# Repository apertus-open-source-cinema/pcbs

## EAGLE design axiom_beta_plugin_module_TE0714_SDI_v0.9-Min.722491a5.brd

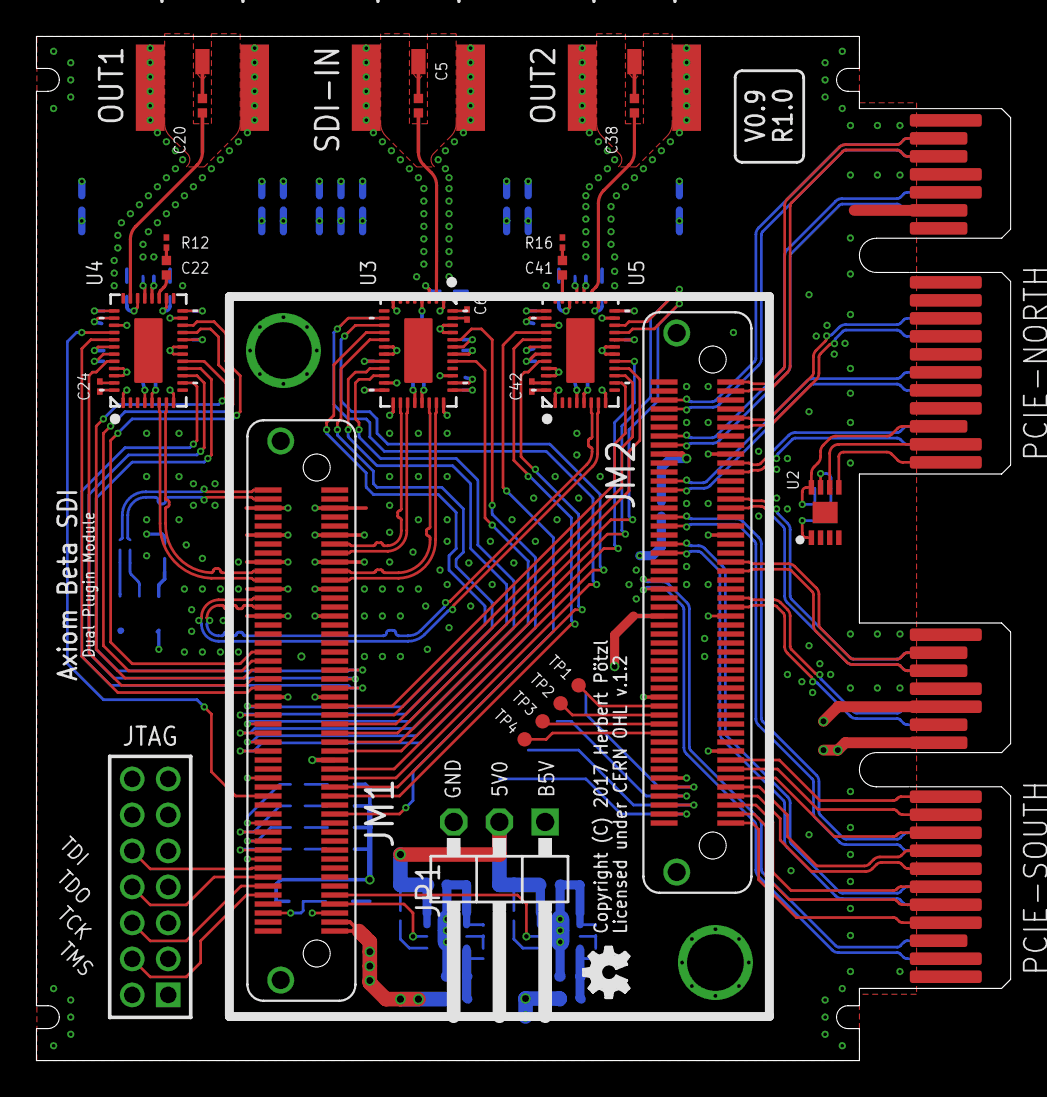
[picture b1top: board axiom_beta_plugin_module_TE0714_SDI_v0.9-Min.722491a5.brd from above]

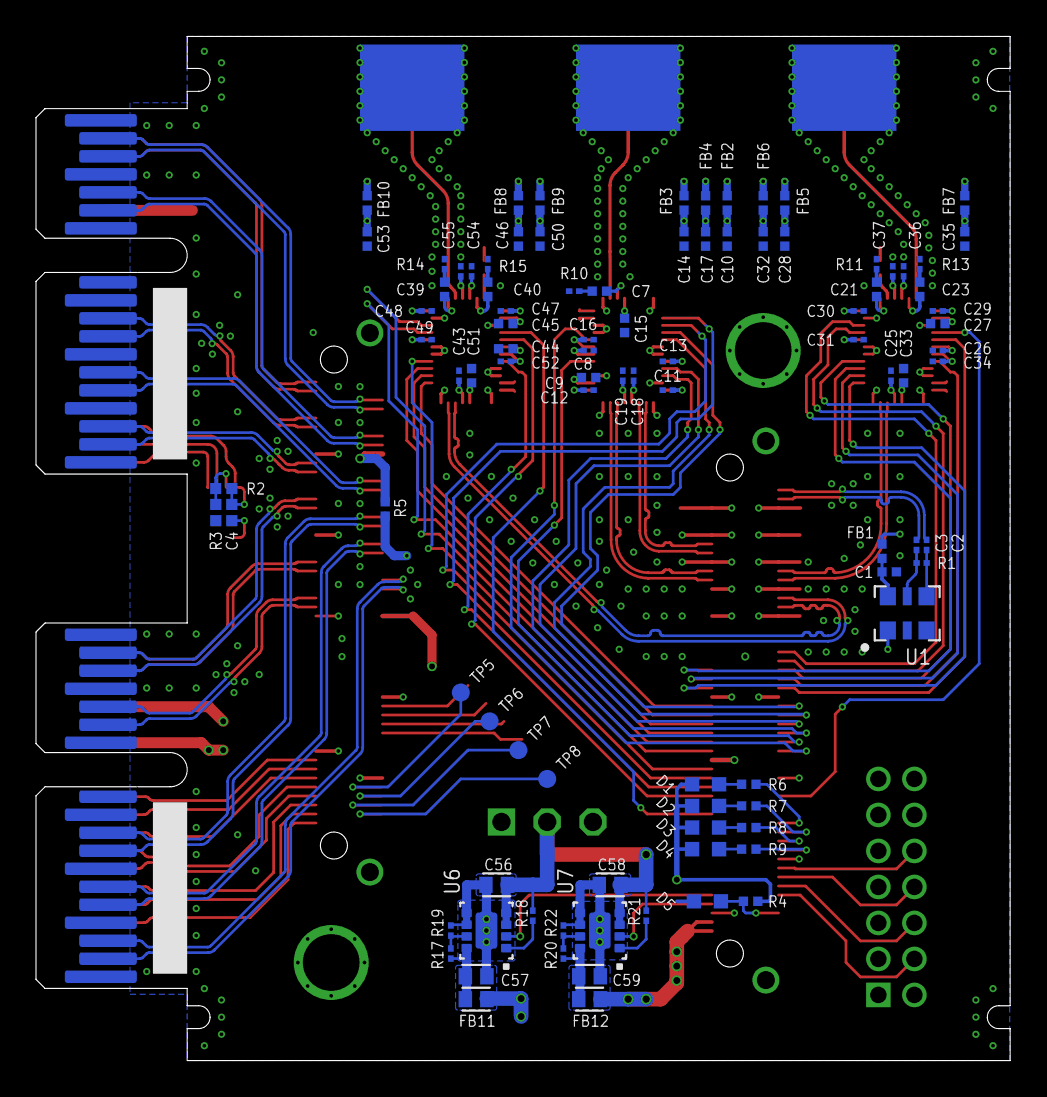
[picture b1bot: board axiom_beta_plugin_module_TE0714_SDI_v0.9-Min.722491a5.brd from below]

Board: 4 copper layers, 54.1 x 56.9 mm, 123 parts (95 on the bottom side), 156 nets.

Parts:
C1: 470n; 0402-C
C2, C3, C11, C12, C13, C18, C19, C25, C29, C30, C31, C36, C37, C43, C47, C48, C49, C54, C55: 100n; 0201-C
C4: 0402-B
C5, C7, C20, C21, C22, C23, C38, C39, C40, C41: 4u7; 0402-C
C6, C24, C42: 470n; 0201-C
C8, C26: 10u; 0201-C
C9, C10, C14, C15, C17, C27, C28, C32, C33, C35, C44, C45, C46, C50, C51, C53: 10u; 0402-C
C16, C34, C52: 1u; 0201-C
C56, C57, C58, C59: 0603-C
D1, D2, D3, D4, D5: LED; CHIPLED_0603
FB1, FB2, FB3, FB4, FB5, FB6, FB7, FB8, FB9, FB10: 0402-C
FB11, FB12: 0603-C
JM1, JM2: LSHM-150-XX.X-XX-DV-A-S
JP1: 1X03/90-S
JTAG: 2X07M
LOGO2: OSHW_LOGO_FILLX0100-NT; OSHW_FILLX100_NOTEXT
OUT1, OUT2: HDBNC; HDBNC_EDGE_2SIDE
PCIE-NORTH: PCIE-36-AXIOM
PCIE-SOUTH: PCIE-36-AXIOM
R1: 100R; 0201-C
R2: 10k; 0402-B
R3: 1k; 0402-B
R4, R6, R7, R8, R9: 10k; 0402-C
R5: 0R; 0402-C
R10, R17, R19, R20, R22: 0201-C
R11, R12, R13, R14, R15, R16: 75R; 0201-C
R18, R21: 10k; 0201-C
SDI-IN: HDBNC; HDBNC_EDGE_2SIDE
TP1, TP2, TP3, TP4: TPTP08R; TP08R
TP5, TP6, TP7, TP8: TPTP10R; TP10R
U1: DSC11XX-3.2X2.5; 3.2X2.5
U2: BR24G04NUX; DFN200X300X100-9N
U3: GS12241; UQFN40P600X400X100-41N
U4, U5: GS12281; UQFN40P600X400X100-41N
U6, U7: TPS82085; MICROSIP

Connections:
1V8: FB2.1, FB3.1, FB4.1, FB5.1, FB6.1, FB8.1, FB9.1, FB11.2, JM1.61, R5.1
3V3: D1.A, D2.A, D3.A, D4.A, FB1.1, FB7.1, FB10.1, FB12.2, JM1.97, JM1.99, R4.2
B14_L0: JM2.99, PCIE-SOUTH.B4
B14_L11_N: JM2.74, TP1.TP
B14_L11_P: JM2.76, TP2.TP
B14_L14_N: JM2.78, TP3.TP
B14_L14_P: JM2.80, TP4.TP
B14_L17_N: JM2.89, PCIE-SOUTH.B9
B14_L17_P: JM2.91, PCIE-SOUTH.B8
B14_L18_N: JM2.85, PCIE-SOUTH.B11
B14_L18_P: JM2.87, PCIE-SOUTH.B10
B14_L19_N: JM2.94, TP6.TP
B14_L19_P: JM2.92, TP5.TP
B14_L20_N: JM2.95, PCIE-SOUTH.B6
B14_L20_P: JM2.93, PCIE-SOUTH.B7
B14_L21_N: JM1.95, U1.1
B14_L21_P: JM1.93, U7.2
B14_L22_N: JM2.96, TP7.TP
B14_L22_P: JM2.98, TP8.TP
B14_L23_P: JM1.91, U6.2
B14_L25: JM2.97, PCIE-SOUTH.B5
B15_L1_N: JM2.14, PCIE-NORTH.A14
B15_L1_P: JM2.16, PCIE-NORTH.A13
B15_L5_N: JM2.8, PCIE-NORTH.A16
B15_L5_P: JM2.6, PCIE-NORTH.A17
B15_L6_N: JM2.26, PCIE-NORTH.A5
B15_L6_P: JM2.24, PCIE-NORTH.A6
B15_L7_N: JM2.1, PCIE-NORTH.B17
B15_L7_P: JM2.3, PCIE-NORTH.B16
B15_L10_N: JM2.11, PCIE-NORTH.A8
B15_L10_P: JM2.9, PCIE-NORTH.A9
B15_L12_N: JM2.34, PCIE-SOUTH.A8
B15_L12_P: JM2.32, PCIE-SOUTH.A9
B15_L13_N: JM2.38, PCIE-SOUTH.A6
B15_L13_P: JM2.40, PCIE-SOUTH.A5
B15_L15_N: JM2.19, PCIE-NORTH.A3
B15_L15_P: JM2.21, PCIE-NORTH.A2
B15_L18_N: JM2.27, PCIE-SOUTH.A17
B15_L18_P: JM2.29, PCIE-SOUTH.A16
B15_L19_N: JM2.41, PCIE-SOUTH.B17
B15_L19_P: JM2.43, PCIE-SOUTH.B16
B15_L22_N: JM2.46, PCIE-SOUTH.A3
B15_L22_P: JM2.48, PCIE-SOUTH.A2
B15_L23_N: JM2.51, PCIE-SOUTH.A13
B15_L23_P: JM2.49, PCIE-SOUTH.A14
B34_L3_N: JM1.42, U4.13
B34_L3_P: JM1.40, U4.17
B34_L4_N: JM1.41, U4.12
B34_L5_N: JM1.45, U4.10
B34_L5_P: JM1.43, U4.11
B34_L7_N: JM1.38, U4.18
B34_L8_N: JM1.52, U3.13
B34_L8_P: JM1.50, U3.12
B34_L9_N: JM1.46, U4.33
B34_L9_P: JM1.44, U4.36
B34_L10_N: JM1.51, U5.11
B34_L10_P: JM1.49, U5.10
B34_L11_N: JM1.53, U5.12
B34_L11_P: JM1.55, U5.17
B34_L12_N: JM1.57, U5.18
B34_L12_P: JM1.59, U5.13
B34_L13_N: JM1.56, U3.18
B34_L13_P: JM1.54, U3.17
B34_L14_N: JM1.60, U3.36
B34_L14_P: JM1.58, U3.33
B34_L16_P: JM1.70, U4.32
B34_L17_N: JM1.63, U3.11
B34_L17_P: JM1.65, U3.10
B34_L19_P: JM1.73, U5.32
B34_L20_N: JM1.76, R6.1
B34_L20_P: JM1.78, R7.1
B34_L21_N: JM1.69, U5.33
B34_L21_P: JM1.67, U5.36
B34_L24_N: JM1.80, R8.1
B34_L24_P: JM1.82, R9.1
DONE: D5.A, JM1.96, R4.1
EN_A: R18.1, U6.1
EN_B: R21.1, U7.1
FB_A: R17.1, R19.2, U6.7
FB_B: R20.1, R22.2, U7.7
GND: C1.2, C4.2, C8.2, C9.2, C10.2, C11.2, C12.2, C13.2, C14.2, C15.2, C16.2, C17.2, C18.2, C19.2, C25.2, C26.2, C27.2, C28.2, C29.2, C30.2, C31.2, C32.2, C33.2, C34.2, C35.2, C36.2, C37.2, C43.2, C44.2, C45.2, C46.2, C47.2, C48.2, C49.2, C50.2, C51.2, C52.2, C53.2, C54.2, C55.2, C56.2, C57.2, C58.2, C59.2, D5.C, JM1.5, JM1.6, JM1.11, JM1.12, JM1.17, JM1.18, JM1.23, JM1.24, JM1.29, JM1.30, JM1.47, JM1.48, JM1.66, JM1.84, JM1.98, JM1.100, JM1.F1, JM1.F2, JM2.17, JM2.35, JM2.36, JM2.72, JM2.83, JM2.90, JM2.F1, JM2.F2, JP1.3, JTAG.1, JTAG.3, JTAG.5, JTAG.7, JTAG.9, JTAG.11, JTAG.13, OUT1.2@1, OUT1.2@2, OUT1.2@3, OUT2.2@1, OUT2.2@2, OUT2.2@3, PCIE-NORTH.A1, PCIE-NORTH.A4, PCIE-NORTH.A7, PCIE-NORTH.A10, PCIE-NORTH.A12, PCIE-NORTH.A15, PCIE-NORTH.A18, PCIE-NORTH.B15, PCIE-NORTH.B18, PCIE-SOUTH.A1, PCIE-SOUTH.A4, PCIE-SOUTH.A7, PCIE-SOUTH.A10, PCIE-SOUTH.A12, PCIE-SOUTH.A15, PCIE-SOUTH.A18, PCIE-SOUTH.B15, PCIE-SOUTH.B18, R3.2, R10.2, R11.2, R12.2, R13.2, R14.2, R15.2, R16.2, R19.1, R22.1, SDI-IN.2@1, SDI-IN.2@2, SDI-IN.2@3, U1.3, U2.1, U2.2, U2.3, U2.4, U2.EP, U3.1, U3.8, U3.14, U3.15, U3.19, U3.21, U3.28, U3.31, U3.37, U3.38, U4.1, U4.8, U4.14, U4.15, U4.19, U4.21, U4.28, U4.31, U4.37, U4.38, U5.1, U5.8, U5.14, U5.15, U5.19, U5.21, U5.28, U5.31, U5.37, U5.38, U6.5, U6.6, U6.EP, U7.5, U7.6, U7.EP
I2C_V: C4.1, PCIE-NORTH.B3, R2.1, U2.8
MGT_CLK0_N: C3.2, JM1.4
MGT_CLK0_P: C2.2, JM1.2
MGT_RX0_N: JM1.21, U3.27
MGT_RX0_P: JM1.19, U3.26
MGT_RX1_N: JM1.15, U3.23
MGT_RX1_P: JM1.13, U3.22
MGT_TX0_N: JM1.28, U5.6
MGT_TX0_P: JM1.26, U5.7
MGT_TX1_N: JM1.22, U4.6
MGT_TX1_P: JM1.20, U4.7
M_1V8: JM2.18, R5.2
unnamed: D1.C, R6.2
unnamed: D2.C, R7.2
unnamed: D3.C, R8.2
unnamed: D4.C, R9.2
unnamed: C6.2, U3.40
unnamed: C6.1, U3.39
unnamed: C24.2, U4.40
unnamed: C24.1, U4.39
unnamed: C9.1, U3.30
unnamed: C8.1, U3.34
unnamed: C21.2, R11.1
unnamed: C21.1, U4.22
unnamed: C22.1, U4.23
unnamed: C22.2, R12.1
unnamed: C23.1, U4.26
unnamed: C23.2, R13.1
unnamed: C7.2, R10.1
unnamed: C7.1, U3.3
unnamed: C27.1, U4.30
unnamed: C26.1, U4.34
unnamed: C20.1, U4.27
unnamed: C25.1, U4.5
unnamed: C20.2, OUT1.1
unnamed: C38.1, U5.23
unnamed: C5.2, U3.2
unnamed: C5.1, SDI-IN.1
unnamed: C38.2, OUT2.1
unnamed: C42.2, U5.40
unnamed: C43.1, U5.5
unnamed: C44.1, U5.34
unnamed: C45.1, U5.30
unnamed: C40.2, R15.1
unnamed: C40.1, U5.26
unnamed: C41.2, R16.1
unnamed: C41.1, U5.27
unnamed: C39.1, U5.22
unnamed: C39.2, R14.1
unnamed: C42.1, U5.39
unnamed: R2.2, R3.1, U2.7
OUT_N: C3.1, R1.2, U1.5
OUT_P: C2.1, R1.1, U1.4
SCL: PCIE-NORTH.B2, U2.6
SDA: PCIE-NORTH.B1, U2.5
S_5V: JP1.1, PCIE-SOUTH.B12
S_VCCIO: JM2.54, PCIE-SOUTH.B14
TCK: JM1.90, JTAG.6
TDI: JM1.86, JTAG.10
TDO: JM1.88, JTAG.8
TMS: JM1.92, JTAG.4
VCCIO0: JM2.53, JTAG.2
VCCO_4: C17.1, C18.1, C19.1, FB4.2, U3.24, U3.25
VCCO_8: C35.1, C36.1, C37.1, FB7.2, U4.24, U4.25
VCCO_9: C53.1, C54.1, C55.1, FB10.2, U5.24, U5.25
VCC_4: C14.1, C15.1, C16.1, FB3.2, U3.4, U3.35
VCC_8: C32.1, C33.1, C34.1, FB6.2, U4.4, U4.35
VCC_9: C50.1, C51.1, C52.1, FB9.2, U5.4, U5.35
VDD_4: C10.1, C11.1, C12.1, C13.1, FB2.2, U3.16, U3.20, U3.29
VDD_8: C28.1, C29.1, C30.1, C31.1, FB5.2, U4.16, U4.20, U4.29
VDD_9: C46.1, C47.1, C48.1, C49.1, FB8.2, U5.16, U5.20, U5.29
VOUT_A: C57.1, FB11.1, R17.2, U6.8
VOUT_B: C59.1, FB12.1, R20.2, U7.8
VSUP: C56.1, C58.1, JP1.2, R18.2, R21.2, U6.3, U6.4, U7.3, U7.4
V_CLK: C1.1, FB1.2, U1.6

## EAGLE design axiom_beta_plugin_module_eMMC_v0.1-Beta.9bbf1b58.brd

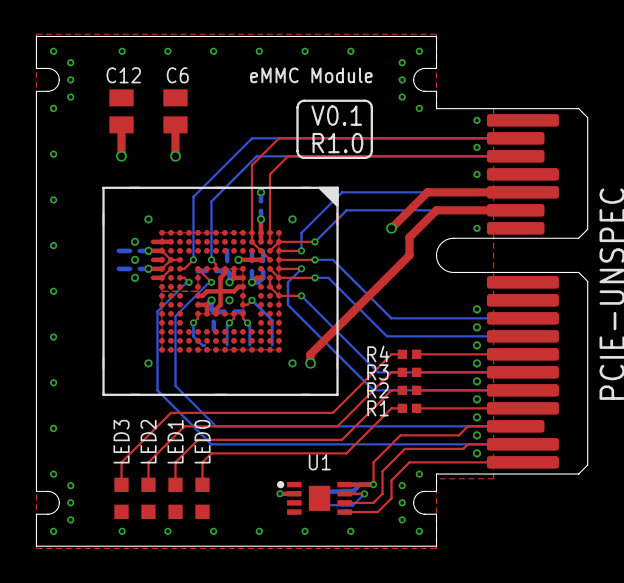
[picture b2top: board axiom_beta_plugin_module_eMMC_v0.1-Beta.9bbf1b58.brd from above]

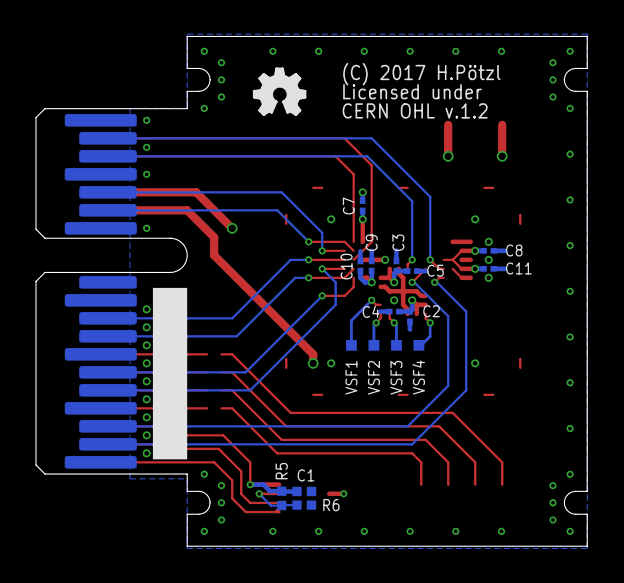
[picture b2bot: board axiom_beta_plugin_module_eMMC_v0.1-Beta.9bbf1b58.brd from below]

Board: 4 copper layers, 30.6 x 28.3 mm, 30 parts (17 on the bottom side), 32 nets.

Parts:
C1: 100n; 0402-C
C2, C3, C8, C9: 100n; 0201-C
C4, C5, C7, C10, C11: 2u2; 0201-C
C6, C12: 22u; 0805-C
LED0, LED1, LED2, LED3: LED; CHIPLED_0603
LOGO2: OSHW_LOGO_FILLX0100-NT; OSHW_FILLX100_NOTEXT
PCIE-UNSPEC: PCIE-36-AXIOM
R1, R2, R3, R4: 0402-C
R5: 10k; 0402-C
R6: 1k; 0402-C
U1: BR24G04NUX; DFN200X300X100-9N
U$1: EMMC-SMD; FBGA153-SMD
VSF1, VSF2, VSF3, VSF4: TPTP06SQ; TP06SQ

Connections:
3V3: C2.1, C3.1, C4.1, C5.1, C6.1, PCIE-UNSPEC.B13, U$1.E6, U$1.F5, U$1.J10, U$1.K9
!RST: PCIE-UNSPEC.A3, U$1.K5
CLK: PCIE-UNSPEC.A2, U$1.M6
CMD: PCIE-UNSPEC.A17, U$1.M5
D0: PCIE-UNSPEC.A14, U$1.A3
D1: PCIE-UNSPEC.A9, U$1.A4
D2: PCIE-UNSPEC.A5, U$1.A5
D3: PCIE-UNSPEC.B16, U$1.B2
D4: PCIE-UNSPEC.A13, U$1.B3
D5: PCIE-UNSPEC.B17, U$1.B4
D6: PCIE-UNSPEC.A8, U$1.B5
D7: PCIE-UNSPEC.A6, U$1.B6
DS: PCIE-UNSPEC.A16, U$1.H5
GND: C1.2, C2.2, C3.2, C4.2, C5.2, C6.2, C7.2, C8.2, C9.2, C10.2, C11.2, C12.2, LED0.C, LED1.C, LED2.C, LED3.C, PCIE-UNSPEC.A1, PCIE-UNSPEC.A4, PCIE-UNSPEC.A7, PCIE-UNSPEC.A10, PCIE-UNSPEC.A12, PCIE-UNSPEC.A15, PCIE-UNSPEC.A18, PCIE-UNSPEC.B15, PCIE-UNSPEC.B18, R6.2, U1.1, U1.2, U1.3, U1.4, U1.EP, U$1.C4, U$1.E7, U$1.G5, U$1.H10, U$1.K8, U$1.N2, U$1.N5, U$1.P4, U$1.P6
I2C_V: C1.1, PCIE-UNSPEC.B3, R5.1, U1.8
LED0: PCIE-UNSPEC.B4, R1.1
LED1: PCIE-UNSPEC.B5, R2.1
LED2: PCIE-UNSPEC.B6, R3.1
LED3: PCIE-UNSPEC.B7, R4.1
unnamed: LED0.A, R1.2
unnamed: LED1.A, R2.2
unnamed: LED2.A, R3.2
unnamed: LED3.A, R4.2
unnamed: R5.2, R6.1, U1.7
unnamed: U$1.E9, VSF1.TP
unnamed: U$1.E10, VSF2.TP
unnamed: U$1.F10, VSF3.TP
unnamed: U$1.K10, VSF4.TP
SCL: PCIE-UNSPEC.B2, U1.6
SDA: PCIE-UNSPEC.B1, U1.5
VCCIO: C8.1, C9.1, C10.1, C11.1, C12.1, PCIE-UNSPEC.B14, U$1.C6, U$1.M4, U$1.N4, U$1.P3, U$1.P5
VDDI: C7.1, U$1.C2

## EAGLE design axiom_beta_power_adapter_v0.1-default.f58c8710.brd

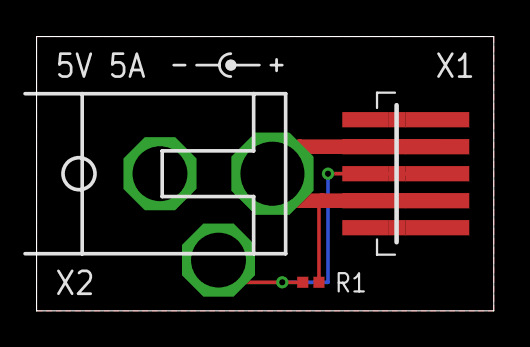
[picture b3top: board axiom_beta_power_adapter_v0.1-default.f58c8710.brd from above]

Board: 2 copper layers, 25.4 x 15.2 mm, 4 parts (1 on the bottom side), 3 nets.

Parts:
LOGO1: OSHW_LOGO_FILLX0100-NT; OSHW_FILLX100_NOTEXT
R1: 0402-B
X1: PICO-SPOX-5
X2: POWER_JACKPTH; POWER_JACK_PTH

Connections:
BETA_5V: R1.1, X1.2, X1.2A, X1.4, X1.4A, X2.PWR
GND: X1.1, X1.1A, X1.5, X1.5A, X2.GND
VIN: R1.2, X1.3, X1.3A, X2.SHUNT

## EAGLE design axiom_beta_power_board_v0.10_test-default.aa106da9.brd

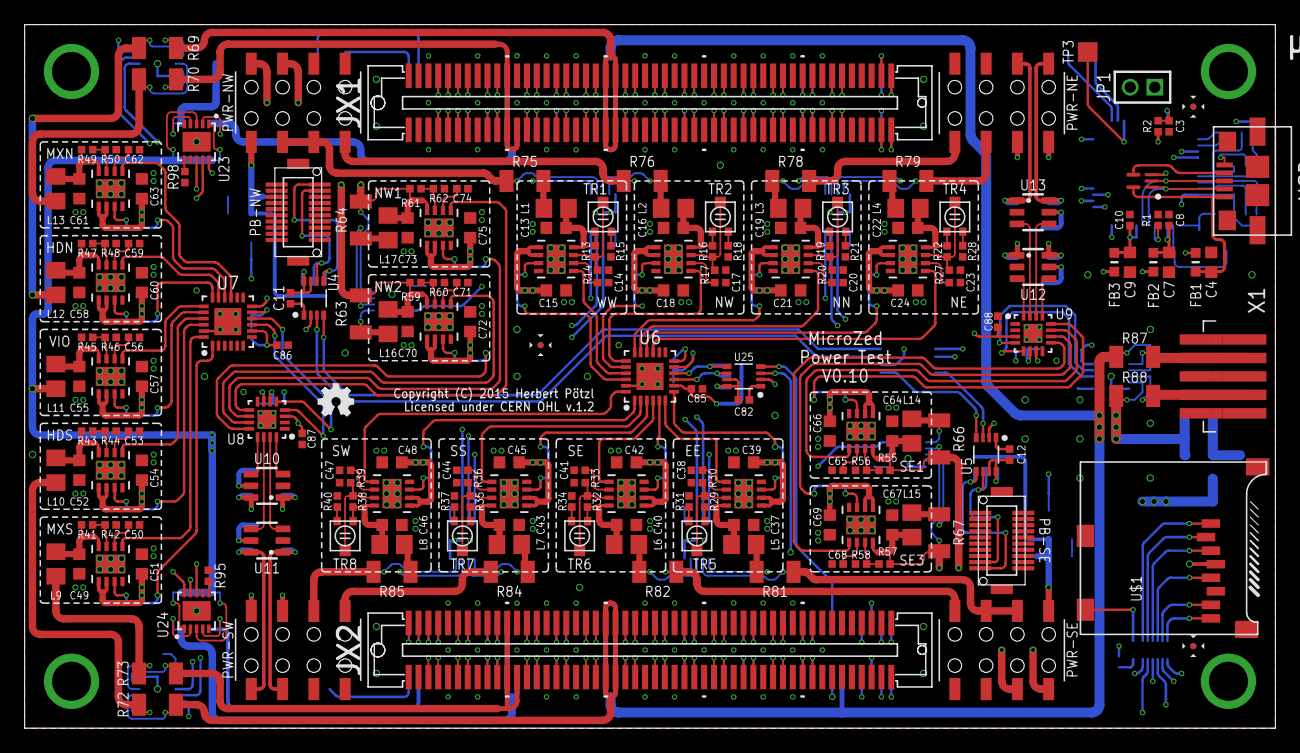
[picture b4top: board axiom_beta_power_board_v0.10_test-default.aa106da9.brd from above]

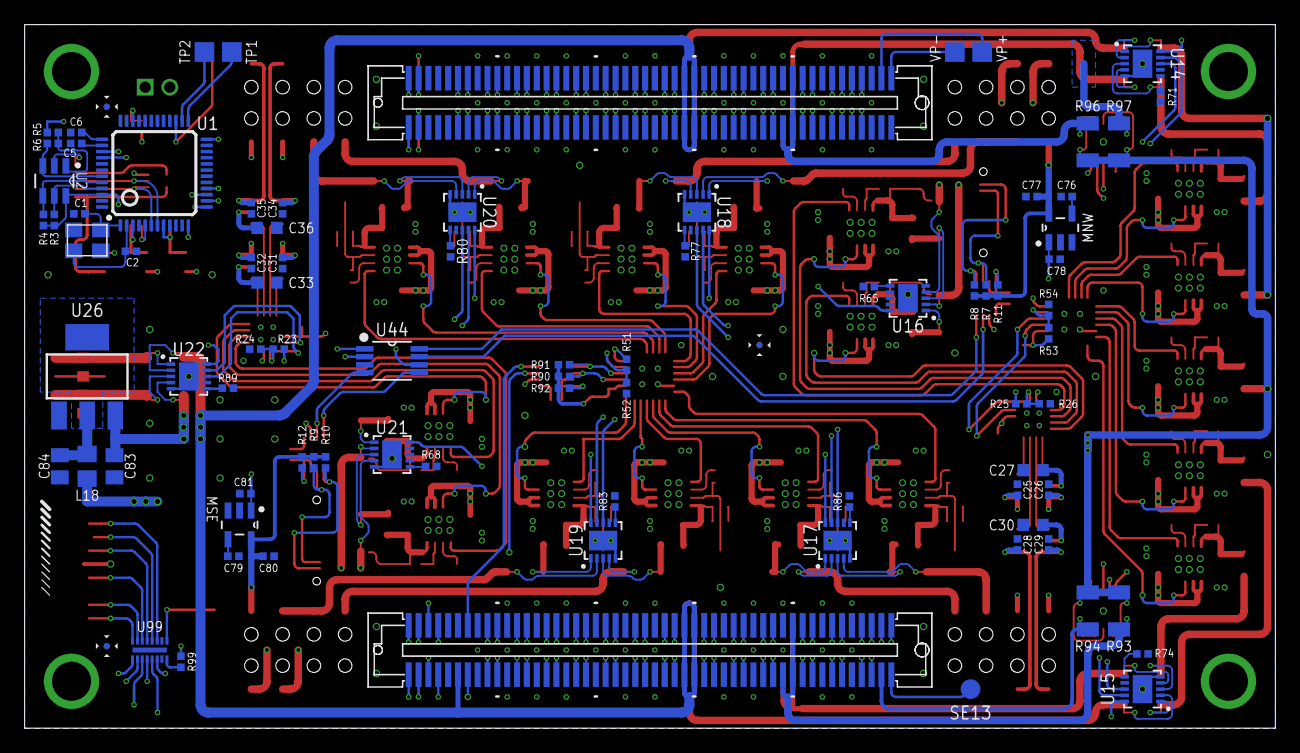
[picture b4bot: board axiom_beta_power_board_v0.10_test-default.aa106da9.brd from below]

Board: 4 copper layers, 101.6 x 57.1 mm, 283 parts (83 on the bottom side), 344 nets.

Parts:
BETA: µZ-FCI-SOCKET-NOHOLES; µZ-SOCKET-NOHOLES
C1, C2, C11, C12, C14, C17, C20, C23, C38, C41, C44, C47, C50, C53, C56, C59, C62, C65, C68, C71, C74, C76, C77, C78, C79, C80, C81, C82, C85, C86, C87, C88: 0402-B
C3: 10n; 0402-B
C4: 100n; 0603-B
C5, C6, C8, C10: 100n; 0402-B
C7, C9: 4µ7; 0603-B
C13, C15, C16, C18, C19, C21, C22, C24, C37, C39, C40, C42, C43, C45, C46, C48, C49, C51, C52, C54, C55, C57, C58, C60, C61, C63, C64, C66, C67, C69, C70, C72, C73, C75: 0603-B
C25, C26, C28, C29, C31, C32, C34, C35: 1µ; 0402-B
C27, C30, C33, C36: 1µ; 0603-B
C83, C84: 0805-B
EE: MCP1727-ADJE/MF; DFN65P300X300X100-9N
FB1, FB2, FB3: 600R; _0603MP
HDN: MCP1727-ADJE/MF; DFN65P300X300X100-9N
HDS: MCP1727-ADJE/MF; DFN65P300X300X100-9N
JP1: 1X02M
L1, L2, L3, L4, L5, L6, L7, L8, L9, L10, L11, L12, L13, L14, L15, L16, L17, L18: 0805-A
LOGO1: OSHW_LOGO_FILLX0100-NT; OSHW_FILLX100_NOTEXT
MNW: SPX3819M5-L; SOT95P280X145-5N
MSE: SPX3819M5-L; SOT95P280X145-5N
MXN: MCP1727-ADJE/MF; DFN65P300X300X100-9N
MXS: MCP1727-ADJE/MF; DFN65P300X300X100-9N
NE: MCP1727-ADJE/MF; DFN65P300X300X100-9N
NN: MCP1727-ADJE/MF; DFN65P300X300X100-9N
NW, NW1, NW2: MCP1727-ADJE/MF; DFN65P300X300X100-9N
PB-NW: DF12(XX)-20DP-0.5V
PB-SE: DF12(XX)-20DP-0.5V
PWR-NE: PINRC-2X04; R2X04
PWR-NW: PINRC-2X04; R2X04
PWR-SE: PINRC-2X04; R2X04
PWR-SW: PINRC-2X04; R2X04
Q1: SMD-4P-2G-3.2X2.5; ABM8G
R1: 12k; 0402-B
R2, R3, R4, R5: 10k; 0402-B
R6: 2k; 0402-B
R7, R8, R9, R10, R11, R12, R13, R14, R15, R16, R17, R18, R19, R20, R21, R22, R23, R24, R25, R26, R27, R28, R29, R30, R31, R32, R33, R34, R35, R36, R37, R38, R39, R40, R41, R42, R43, R44, R45, R46, R47, R48, R49, R50, R51, R52, R53, R54, R55, R56, R57, R58, R59, R60, R61, R62, R65, R68, R71, R74, R77, R80, R83, R86, R89, R90, R91, R92, R95, R98, R99: 0402-B
R63, R64, R66, R67, R69, R70, R72, R73, R75, R76, R78, R79, R81, R82, R84, R85, R87, R88, R93, R94, R96, R97: 1206-B
SE, SE1, SE3: MCP1727-ADJE/MF; DFN65P300X300X100-9N
SE13: TPTP16R; TP16R
SS: MCP1727-ADJE/MF; DFN65P300X300X100-9N
SW: MCP1727-ADJE/MF; DFN65P300X300X100-9N
TP1, TP2, TP3: TPTP16SQ; TP16SQ
TR1, TR2, TR3, TR4, TR5, TR6, TR7, TR8: PVZ2A; TRIM-PVZ2A
U1: FT232H; LQFP48
U2: 93LC46BT-I/OT; SOT95P280X145-6N
U3: TPD3E001DRLR; SOT50P160X60-5N
U4, U5, U25: GTL2002DC; VSSOP-8
U6, U7: MCP23018QFN; QFN50P400X400X80-25N
U8, U9: MCP23009-E/MG; QFN50P300X300X80-17N
U10, U11, U12, U13: SOT23-6
U14, U15, U16, U17, U18, U19, U20, U21, U22, U23, U24: PAC1720; DFN3X3_10LEAD
U26: LD1117S; SOT-223
U44: PCA9540BDP; SOP65P490X110-8N
U99: IP4251CZ16-8-TTL; SON40P135X330X55-17N
U$1: MICRO-SD-2CD; TF-MICRO-SD_PP2
USB: 5_USB_3S; MICRO-AB-H-SMT
VIO: MCP1727-ADJE/MF; DFN65P300X300X100-9N
VP+: TPTP16SQ; TP16SQ
VP-: TPTP16SQ; TP16SQ
WW: MCP1727-ADJE/MF; DFN65P300X300X100-9N
X1: PICO-SPOX-5
ZED: µZ-FCI-CONONLY; µZ-CONONLY

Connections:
A_SCL: PB-NW.2, R8.2, U4.5
A_SCL': U4.4, U44.8
A_SDA: PB-NW.4, R7.2, U4.6
A_SDA': U4.3, U44.7
BANK13_00_N: BETA.87, ZED.87
BANK13_00_P: BETA.89, ZED.89
BANK13_01_N: BETA.90, ZED.90
BANK13_01_P: BETA.88, ZED.88
BANK13_02_N: BETA.91, ZED.91
BANK13_02_P: BETA.93, ZED.93
BANK13_03_N: BETA.92, ZED.92
BANK13_03_P: BETA.94, ZED.94
BANK13_04_N: BETA.193, ZED.193
BANK13_04_P: BETA.195, ZED.195
BANK13_05_N: BETA.196, ZED.196
BANK13_05_P: BETA.194, ZED.194
BANK13_06_N: BETA.199, ZED.199
BANK13_06_P: BETA.197, ZED.197
BANK13_SE_0: SE13.TP, ZED.200
BETA_5V: R88.1, U22.3, X1.4, X1.4A
BETA_5V': C15.1, C18.1, C21.1, C24.1, C27.1, C30.1, C33.1, C36.1, C39.1, C42.1, C45.1, C48.1, C51.1, C54.1, C57.1, C60.1, C63.1, C66.1, C69.1, C72.1, C75.1, C78.1, C81.1, C83.1, EE.1, EE.2, HDN.1, HDN.2, HDS.1, HDS.2, MNW.1, MSE.1, MXN.1, MXN.2, MXS.1, MXS.2, NE.1, NE.2, NN.1, NN.2, NW.1, NW.2, NW1.1, NW1.2, NW2.1, NW2.2, R88.2, SE.1, SE.2, SE1.1, SE1.2, SE3.1, SE3.2, SS.1, SS.2, SW.1, SW.2, U10.5, U11.5, U12.5, U13.5, U22.4, U26.3, VIO.1, VIO.2, WW.1, WW.2
BETA_TDO: BETA.3, JP1.2
B_SCL: PB-SE.2, R10.2, U5.5
B_SCL': U5.4, U44.5
B_SDA: PB-SE.4, R9.2, U5.6
B_SDA': U5.3, U44.4
CD: U99.1, U$1.CD1
CLK: U99.6, U$1.5
CMD: U99.5, U$1.3
DAT0: U99.7, U$1.7
DAT1: U99.8, U$1.8
DAT2: U99.3, U$1.1
DAT3: U99.4, U$1.2
EE_CLK1: R4.1, U1.44, U2.4
EE_CS1: R3.1, U1.45, U2.5
EE_DATA1: R6.2, U1.43, U2.3
EN1: U8.13, U10.4
EN1B: U9.13, U12.4
EN2: U8.14, U11.4
EN2B: U9.14, U13.4
EN3: U8.16, U10.3
EN3B: U9.16, U12.3
EN4: U8.15, U11.3
EN4B: U9.15, U13.3
E_I2C_V: C34.1, PWR-NE.4, U13.1
E_SDI_V: C35.1, PWR-NE.2, U13.6
E_VE: PWR-SE.4, PWR-SE.6, R81.2, U19.2
E_VE': L5.2, R81.1, U19.1
FTDI_D_N: U1.6, U3.1, USB.2
FTDI_D_P: U1.7, U3.2, USB.3
FTDI_TCK: BETA.1, U1.13, ZED.1
FTDI_TDI: BETA.4, U1.14
FTDI_TDO: U1.15, ZED.3
FTDI_TMS: BETA.2, U1.16, ZED.2
GND: BETA.15, BETA.16, BETA.21, BETA.22, BETA.27, BETA.28, BETA.33, BETA.34, BETA.39, BETA.40, BETA.45, BETA.46, BETA.51, BETA.52, BETA.65, BETA.66, BETA.71, BETA.72, BETA.77, BETA.85, BETA.86, BETA.95, BETA.96, BETA.115, BETA.116, BETA.121, BETA.122, BETA.127, BETA.128, BETA.133, BETA.134, BETA.139, BETA.140, BETA.145, BETA.146, BETA.151, BETA.152, BETA.165, BETA.166, BETA.171, BETA.172, BETA.177, BETA.185, BETA.186, BETA.191, BETA.192, C1.2, C2.2, C3.2, C4.2, C5.2, C6.2, C7.2, C8.2, C9.2, C10.2, C11.2, C12.2, C13.2, C14.2, C15.2, C16.2, C17.2, C18.2, C19.2, C20.2, C21.2, C22.2, C23.2, C24.2, C25.2, C26.2, C27.2, C28.2, C29.2, C30.2, C31.2, C32.2, C33.2, C34.2, C35.2, C36.2, C37.2, C38.2, C39.2, C40.2, C41.2, C42.2, C43.2, C44.2, C45.2, C46.2, C47.2, C48.2, C49.2, C50.2, C51.2, C52.2, C53.2, C54.2, C55.2, C56.2, C57.2, C58.2, C59.2, C60.2, C61.2, C62.2, C63.2, C64.2, C65.2, C66.2, C67.2, C68.2, C69.2, C70.2, C71.2, C72.2, C73.2, C74.2, C75.2, C76.2, C77.2, C78.2, C79.2, C80.2, C81.2, C82.2, C83.2, C84.2, C85.2, C86.2, C87.2, C88.2, EE.4, EE.9, HDN.4, HDN.9, HDS.4, HDS.9, MNW.2, MSE.2, MXN.4, MXN.9, MXS.4, MXS.9, NE.4, NE.9, NN.4, NN.9, NW.4, NW.9, NW1.4, NW1.9, NW2.4, NW2.9, PB-NW.6, PB-NW.7, PB-NW.10, PB-NW.13, PB-NW.18, PB-SE.6, PB-SE.7, PB-SE.10, PB-SE.13, PB-SE.18, PWR-NW.5, PWR-NW.7, PWR-SE.5, PWR-SE.7, Q1.2, Q1.4, R1.1, R14.2, R15.2, R17.2, R18.2, R20.2, R21.2, R24.2, R26.2, R27.2, R28.2, R30.2, R31.2, R33.2, R34.2, R36.2, R37.2, R39.2, R40.2, R42.2, R44.2, R46.2, R48.2, R50.2, R52.2, R54.2, R56.2, R58.2, R60.2, R62.2, R65.2, R68.2, R71.2, R74.2, R77.2, R80.2, R83.2, R86.2, R89.2, R95.2, R98.2, SE.4, SE.9, SE1.4, SE1.9, SE3.4, SE3.9, SS.4, SS.9, SW.4, SW.9, U1.4, U1.9, U1.10, U1.11, U1.22, U1.23, U1.35, U1.36, U1.41, U1.47, U1.48, U2.2, U3.3, U4.1, U5.1, U6.23, U7.23, U8.1, U9.1, U10.2, U11.2, U12.2, U13.2, U14.5, U14.EPAD, U15.5, U15.EPAD, U16.5, U16.EPAD, U17.5, U17.EPAD, U18.5, U18.EPAD, U19.5, U19.EPAD, U20.5, U20.EPAD, U21.5, U21.EPAD, U22.5, U22.EPAD, U23.5, U23.EPAD, U24.5, U24.EPAD, U25.1, U26.1, U44.6, U99.17, U$1.6, U$1.CD2, USB.5, VIO.4, VIO.9, WW.4, WW.9, X1.1, X1.1A, X1.5, X1.5A, ZED.15, ZED.16, ZED.21, ZED.22, ZED.27, ZED.28, ZED.33, ZED.34, ZED.39, ZED.40, ZED.45, ZED.46, ZED.51, ZED.52, ZED.65, ZED.66, ZED.71, ZED.72, ZED.77, ZED.85, ZED.86, ZED.95, ZED.96, ZED.115, ZED.116, ZED.121, ZED.122, ZED.127, ZED.128, ZED.133, ZED.134, ZED.139, ZED.140, ZED.145, ZED.146, ZED.151, ZED.152, ZED.165, ZED.166, ZED.171, ZED.172, ZED.177, ZED.185, ZED.186, ZED.191, ZED.192
GPA0_C: NE.5, U6.15
GPA0_W: MXN.5, U7.15
GPA1_C: NE.3, U6.16
GPA1_W: MXN.3, U7.16
GPA2_C: NN.5, U6.17
GPA2_W: HDN.5, U7.17
GPA3_C: NN.3, U6.18
GPA3_W: HDN.3, U7.18
GPA4_C: NW.5, U6.19
GPA4_W: U7.19, VIO.5
GPA5_C: NW.3, U6.20
GPA5_W: U7.20, VIO.3
GPA6_C: U6.21, WW.5
GPA6_W: HDS.5, U7.21
GPA7_C: U6.22, WW.3
GPA7_W: HDS.3, U7.22
GPB0_C: SW.5, U6.24
GPB0_W: MXS.5, U7.24
GPB1_C: SW.3, U6.1
GPB1_W: MXS.3, U7.1
GPB2_C: SS.5, U6.2
GPB3_C: SS.3, U6.3
GPB4_C: SE.5, U6.4
GPB5_C: SE.3, U6.5
GPB6_C: EE.5, U6.6
GPB7_C: EE.3, U6.7
JTAG_V: C29.1, PWR-SW.2, U11.6
JX1_00_N: BETA.13, ZED.13
JX1_00_P: BETA.11, ZED.11
JX1_01_N: BETA.14, ZED.14
JX1_01_P: BETA.12, ZED.12
JX1_02_N: BETA.19, ZED.19
JX1_02_P: BETA.17, ZED.17
JX1_03_N: BETA.20, ZED.20
JX1_03_P: BETA.18, ZED.18
JX1_04_N: BETA.25, ZED.25
JX1_04_P: BETA.23, ZED.23
JX1_05_N: BETA.26, ZED.26
JX1_05_P: BETA.24, ZED.24
JX1_06_N: BETA.31, ZED.31
JX1_06_P: BETA.29, ZED.29
JX1_07_N: BETA.32, ZED.32
JX1_07_P: BETA.30, ZED.30
JX1_08_N: BETA.37, ZED.37
JX1_08_P: BETA.35, ZED.35
JX1_09_N: BETA.38, ZED.38
JX1_09_P: BETA.36, ZED.36
JX1_10_N: BETA.43, ZED.43
JX1_10_P: BETA.41, ZED.41
JX1_11_N: BETA.44, ZED.44
JX1_11_P: BETA.42, ZED.42
JX1_12_N: BETA.49, ZED.49
JX1_12_P: BETA.47, ZED.47
JX1_13_N: BETA.50, ZED.50
JX1_13_P: BETA.48, ZED.48
JX1_14_N: BETA.55, ZED.55
JX1_14_P: BETA.53, ZED.53
JX1_15_N: BETA.56, ZED.56
JX1_15_P: BETA.54, ZED.54
JX1_16_N: BETA.63, ZED.63
JX1_16_P: BETA.61, ZED.61
JX1_17_N: BETA.64, ZED.64
JX1_17_P: BETA.62, ZED.62
JX1_18_N: BETA.69, ZED.69
JX1_18_P: BETA.67, ZED.67
JX1_19_N: BETA.70, ZED.70
JX1_19_P: BETA.68, ZED.68
JX1_20_N: BETA.75, ZED.75
JX1_20_P: BETA.73, ZED.73
JX1_21_N: BETA.76, ZED.76
JX1_21_P: BETA.74, ZED.74
JX1_22_N: BETA.83, ZED.83
JX1_22_P: BETA.81, ZED.81
JX1_23_N: BETA.84, ZED.84
JX1_23_P: BETA.82, ZED.82
JX2_00_N: BETA.119, ZED.119
JX2_00_P: BETA.117, ZED.117
JX2_01_N: BETA.120, ZED.120
JX2_01_P: BETA.118, ZED.118
JX2_02_N: BETA.125, ZED.125
JX2_02_P: BETA.123, ZED.123
JX2_03_N: BETA.126, ZED.126
JX2_03_P: BETA.124, ZED.124
JX2_04_N: BETA.131, ZED.131
JX2_04_P: BETA.129, ZED.129
JX2_05_N: BETA.132, ZED.132
JX2_05_P: BETA.130, ZED.130
JX2_06_N: BETA.137, ZED.137
JX2_06_P: BETA.135, ZED.135
JX2_07_N: BETA.138, ZED.138
JX2_07_P: BETA.136, ZED.136
JX2_08_N: BETA.143, ZED.143
JX2_08_P: BETA.141, ZED.141
JX2_09_N: BETA.144, ZED.144
JX2_09_P: BETA.142, ZED.142
JX2_10_N: BETA.149, ZED.149
JX2_10_P: BETA.147, ZED.147
JX2_11_N: BETA.150, ZED.150
JX2_11_P: BETA.148, ZED.148
JX2_12_N: BETA.155, ZED.155
JX2_12_P: BETA.153, ZED.153
JX2_13_N: BETA.156, ZED.156
JX2_13_P: BETA.154, ZED.154
JX2_14_N: BETA.163, ZED.163
JX2_14_P: BETA.161, ZED.161
JX2_15_N: BETA.164, ZED.164
JX2_15_P: BETA.162, ZED.162
JX2_16_N: BETA.169, ZED.169
JX2_16_P: BETA.167, ZED.167
JX2_17_N: BETA.170, ZED.170
JX2_17_P: BETA.168, ZED.168
JX2_18_N: BETA.175, ZED.175
JX2_18_P: BETA.173, ZED.173
JX2_19_N: BETA.176, ZED.176
JX2_19_P: BETA.174, ZED.174
JX2_20_N: BETA.183, ZED.183
JX2_20_P: BETA.181, ZED.181
JX2_21_N: BETA.184, ZED.184
JX2_21_P: BETA.182, ZED.182
JX2_22_N: BETA.189, ZED.189
JX2_22_P: BETA.187, ZED.187
JX2_23_N: BETA.190, ZED.190
JX2_23_P: BETA.188, ZED.188
JX2_SE_0: U25.4, ZED.113
JX2_SE_1: U25.3, ZED.114
MP-NW-1: PWR-NW.3, R64.2, U16.4
MP-NW-1': L17.2, R64.1, U16.3
MP-NW-2: PWR-NW.1, R63.2, U16.2
MP-NW-2': L16.2, R63.1, U16.1
MP-SE-1: PWR-SE.1, R66.2, U21.2
MP-SE-1': L14.2, R66.1, U21.1
MP-SE-3: PWR-SE.3, R67.2, U21.4
MP-SE-3': L15.2, R67.1, U21.3
M_V_NW: C77.1, MNW.5, PWR-NW.2, R7.1, R8.1, R11.1
M_V_SE: C80.1, MSE.5, PWR-SE.2, R9.1, R10.1, R12.1
unnamed: C49.1, L9.1, MXS.8, R41.1
unnamed: R77.1, U18.6
unnamed: C11.1, R11.2, U4.7, U4.8
unnamed: C12.1, R12.2, U5.7, U5.8
unnamed: C13.1, L1.1, R13.1, TR1.1, WW.8
unnamed: TP1.TP, U1.25
unnamed: TP2.TP, U1.26
unnamed: R95.1, U24.6
unnamed: R13.2, R14.1, TR1.2, WW.7
unnamed: R15.1, TR1.3
unnamed: MXS.7, R41.2, R42.1
unnamed: C50.1, MXS.6
unnamed: C64.1, L14.1, R55.1, SE1.8
unnamed: R55.2, R56.1, SE1.7
unnamed: VP+.TP, ZED.97
unnamed: VP-.TP, ZED.99
unnamed: R98.1, U23.6
unnamed: TP3.TP, U1.27
unnamed: R99.2, U99.16
unnamed: C14.1, WW.6
unnamed: C65.1, SE1.6
unnamed: C67.1, L15.1, R57.1, SE3.8
unnamed: R5.1, R6.1, U2.1
unnamed: C1.1, Q1.1, U1.1
unnamed: C2.1, Q1.3, U1.2
unnamed: C3.1, R2.1, U1.34
unnamed: R1.2, U1.5
unnamed: U3.4, USB.4
unnamed: R23.2, R24.1, U9.6
unnamed: R25.2, R26.1, U8.6
unnamed: C16.1, L2.1, NW.8, R16.1, TR2.1
unnamed: NW.7, R16.2, R17.1, TR2.2
unnamed: R18.1, TR2.3
unnamed: C17.1, NW.6
unnamed: R57.2, R58.1, SE3.7
unnamed: C68.1, SE3.6
unnamed: R80.1, U20.6
unnamed: C19.1, L3.1, NN.8, R19.1, TR3.1
unnamed: NN.7, R19.2, R20.1, TR3.2
unnamed: R21.1, TR3.3
unnamed: C20.1, NN.6
unnamed: C70.1, L16.1, NW2.8, R59.1
unnamed: NW2.7, R59.2, R60.1
unnamed: R83.1, U19.6
unnamed: C22.1, L4.1, NE.8, R22.1, TR4.1
unnamed: NE.7, R22.2, R27.1, TR4.2
unnamed: R28.1, TR4.3
unnamed: C23.1, NE.6
unnamed: C71.1, NW2.6
unnamed: C73.1, L17.1, NW1.8, R61.1
unnamed: R86.1, U17.6
unnamed: C37.1, EE.8, L5.1, R29.1, TR5.1
unnamed: EE.7, R29.2, R30.1, TR5.2
unnamed: R31.1, TR5.3
unnamed: C38.1, EE.6
unnamed: NW1.7, R61.2, R62.1
unnamed: C74.1, NW1.6
unnamed: R65.1, U16.6
unnamed: C40.1, L6.1, R32.1, SE.8, TR6.1
unnamed: R32.2, R33.1, SE.7, TR6.2
unnamed: R34.1, TR6.3
unnamed: C41.1, SE.6
unnamed: C82.1, R92.2, U25.7, U25.8
unnamed: C43.1, L7.1, R35.1, SS.8, TR7.1
unnamed: R35.2, R36.1, SS.7, TR7.2
unnamed: R37.1, TR7.3
unnamed: C44.1, SS.6
unnamed: R68.1, U21.6
unnamed: C46.1, L8.1, R38.1, SW.8, TR8.1
unnamed: R38.2, R39.1, SW.7, TR8.2
unnamed: R40.1, TR8.3
unnamed: C47.1, SW.6
unnamed: R71.1, U14.6
unnamed: R74.1, U15.6
unnamed: C52.1, HDS.8, L10.1, R43.1
unnamed: HDS.7, R43.2, R44.1
unnamed: C53.1, HDS.6
unnamed: R89.1, U22.6
unnamed: C55.1, L11.1, R45.1, VIO.8
unnamed: R45.2, R46.1, VIO.7
unnamed: C56.1, VIO.6
unnamed: C58.1, HDN.8, L12.1, R47.1
unnamed: HDN.7, R47.2, R48.1
unnamed: C59.1, HDN.6
unnamed: C76.1, MNW.4
unnamed: C61.1, L13.1, MXN.8, R49.1
unnamed: MXN.7, R49.2, R50.1
unnamed: C62.1, MXN.6
unnamed: R51.2, R52.1, U6.11
unnamed: R53.2, R54.1, U7.11
unnamed: C79.1, MSE.4
N_I2C_V: C32.1, PWR-NE.1, U12.6
N_SPI_V: C31.1, PWR-NE.3, U12.1
N_VE: PWR-NE.5, R79.2, U20.4
N_VE': L4.2, R79.1, U20.3
N_VN: PWR-NE.7, R78.2, U20.2
N_VN': L3.2, R78.1, U20.1
N_VW: PWR-NW.8, R76.2, U18.4
N_VW': L2.2, R76.1, U18.3
PCIE_N_V: BETA.78, BETA.79, BETA.80, R70.2, U14.4
PCIE_N_V': L13.2, R70.1, U14.3
PCIE_S_V: BETA.178, BETA.179, BETA.180, R73.2, U15.4
PCIE_S_V': L9.2, R73.1, U15.3
PMOD_D0: U99.9, ZED.101
PMOD_D1: U99.10, ZED.102
PMOD_D2: U99.12, ZED.103
PMOD_D3: U99.11, ZED.104
PMOD_D6: U99.14, ZED.107
PMOD_D7: U99.13, ZED.108
PMOD_SCL: U44.1, ZED.105
PMOD_SDA: U44.2, ZED.106
REGOUT: C84.1, L18.1, U26.2, U26.TER
SCL: R90.2, U6.9, U7.9, U8.4, U9.4, U14.9, U15.9, U17.9, U18.9, U19.9, U20.9, U22.9, U23.9, U24.9, U25.6
SDA: R91.2, U6.10, U7.10, U8.5, U9.5, U14.8, U15.8, U17.8, U18.8, U19.8, U20.8, U22.8, U23.8, U24.8, U25.5
S_I2C_V: C26.1, PWR-SW.1, U10.6
S_SPI_V: C25.1, PWR-SW.3, U10.1
S_VE: PWR-SE.8, R82.2, U19.4
S_VE': L6.2, R82.1, U19.3
S_VS: PWR-SW.7, R84.2, U17.2
S_VS': L7.2, R84.1, U17.1
S_VW: PWR-SW.5, R85.2, U17.4
S_VW': L8.2, R85.1, U17.3
U26_PWRGD: SE1.5, U9.11
U26_SHDN: SE1.3, U9.12
U27_PWRGD: SE3.5, U9.9
U27_SHDN: SE3.3, U9.10
U28_PWRGD: NW2.5, U8.11
U28_SHDN: NW2.3, U8.12
U29_PWRGD: NW1.5, U8.9
U29_SHDN: NW1.3, U8.10
U43_SENSE2-: R97.2, U23.4
VBUS: C4.1, FB1.1, U3.5, USB.1
VCC: C85.1, C86.1, C87.1, C88.1, L18.2, R23.1, R25.1, R51.1, R53.1, R90.1, R91.1, R92.1, R99.1, U6.8, U6.12, U7.8, U7.12, U8.3, U8.7, U9.3, U9.7, U14.10, U15.10, U16.10, U17.10, U18.10, U19.10, U20.10, U21.10, U22.10, U23.10, U24.10, U$1.4
VCCA: C6.1, U1.37
VCCD: FB2.1, FB3.1, R2.2, R3.2, R4.2, R5.2, U1.12, U1.24, U1.39, U1.46, U2.6
VCCIO: L11.2, R93.1, R94.1, R96.1, R97.1, U4.2, U5.2, U23.1, U23.3, U24.1, U24.3, U25.2
VCCO_13: R94.2, U24.4, ZED.198
VCCO_34: R96.2, U23.2, ZED.78, ZED.79, ZED.80
VCCO_35: R93.2, U24.2, ZED.178, ZED.179, ZED.180
VCORE: C5.1, U1.38
VIN: X1.3, X1.3A
VIN_HDR_N: BETA.57, BETA.58, BETA.59, BETA.60, R69.2, U14.2
VIN_HDR_N': L12.2, R69.1, U14.1
VIN_HDR_S: BETA.157, BETA.158, BETA.159, BETA.160, R72.2, U15.2
VIN_HDR_S': L10.2, R72.1, U15.1
VPHY: C7.1, C8.1, FB2.2, U1.3
VPLL: C9.1, C10.1, FB3.2, U1.8
VREGIN: FB1.2, U1.40
W_I2C_V: C28.1, PWR-SW.4, U11.1
W_VW: PWR-NW.4, PWR-NW.6, R75.2, U18.2
W_VW': L1.2, R75.1, U18.1
ZED_5V: R87.1, U22.1, X1.2, X1.2A
ZED_5V': R87.2, U22.2, ZED.57, ZED.58, ZED.59, ZED.60, ZED.112, ZED.157, ZED.158, ZED.159, ZED.160
ZED_TDI: JP1.1, ZED.4

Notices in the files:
axiom_beta_plugin_module_TE0714_SDI_v0.9-Min.722491a5.brd:
Copyright (C) 2017 Herbert Pötzl
Licensed under CERN OHL v.1.2
axiom_beta_plugin_module_eMMC_v0.1-Beta.9bbf1b58.brd:
(C) 2017 H.Pötzl
CERN OHL v.1.2
axiom_beta_power_adapter_v0.1-default.f58c8710.brd:
Copyright (C) 2015
axiom_beta_power_board_v0.10_test-default.aa106da9.brd:
Copyright (C) 2015 Herbert Pötzl
parts and their libraries:
microbuilder: This work is placed in the public domain, and may be freely used for commercial and non-commercial work with the following conditions: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
